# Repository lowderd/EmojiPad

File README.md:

# EmojiPad
ATmega328 Based USB HID Keyboard

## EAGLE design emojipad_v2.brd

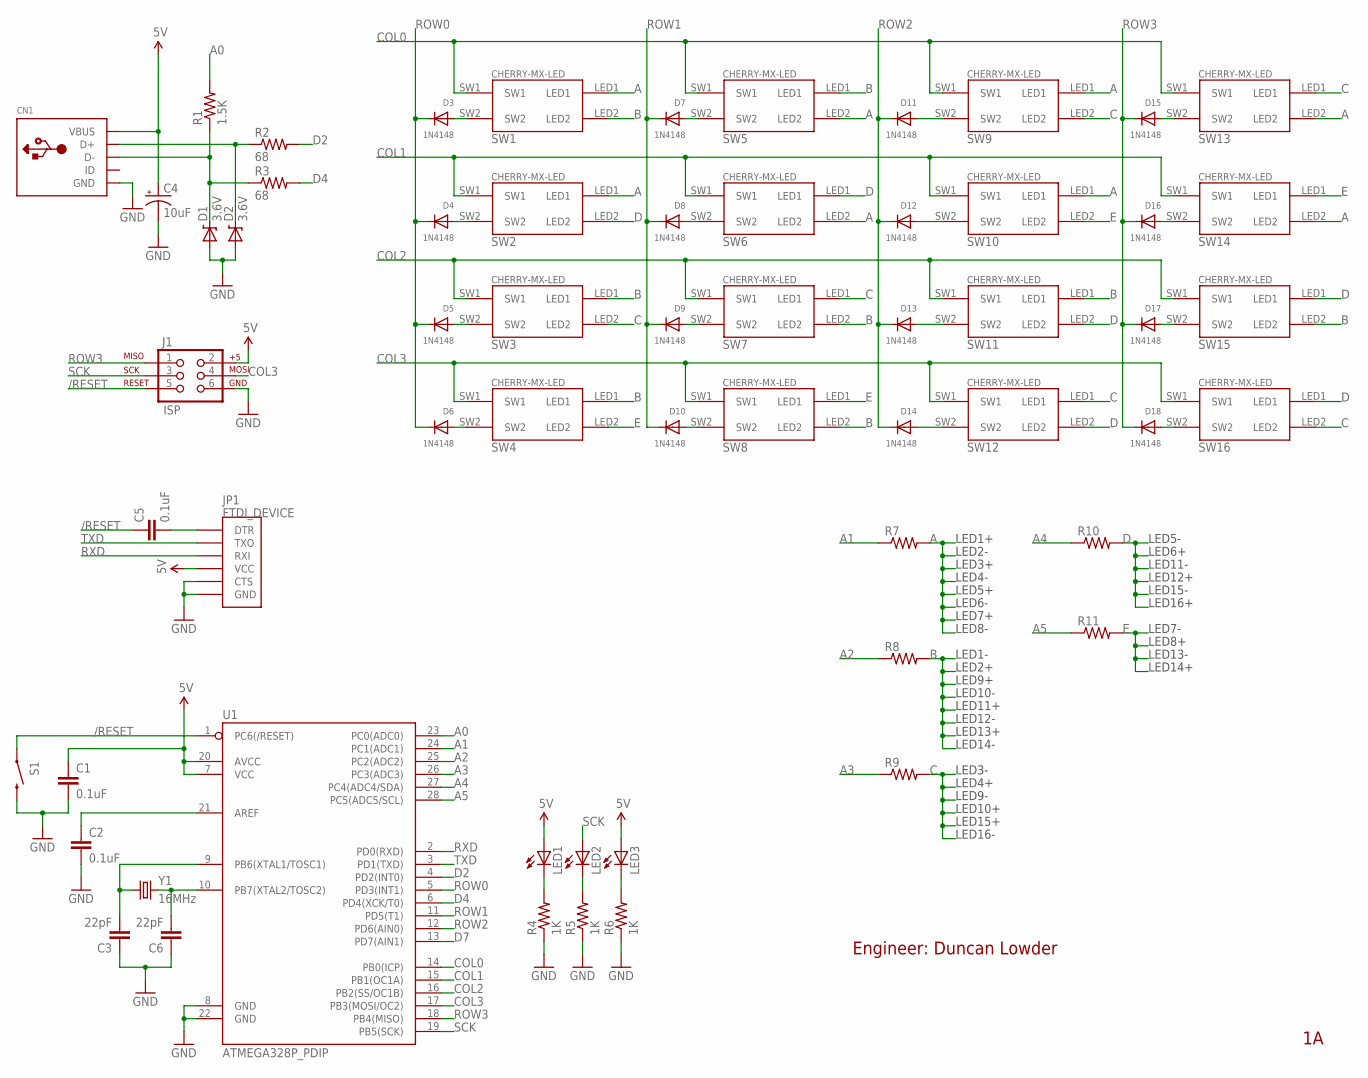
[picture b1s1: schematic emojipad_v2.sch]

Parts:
C1, C2, C5: 0.1uF; CAP-PTH-SMALL
C3, C6: 22pF; CAP-PTH-SMALL
C4: 10uF; CPOL-RADIAL-10UF-25V
CN1: USBMOLEX; USB-MINIB-THM-MOLEX
D1, D2: 3.6V; DIODE-ZENER
D3, D4, D5, D6, D7, D8, D9, D10, D11, D12, D13, D14, D15, D16, D17, D18: 1N4148; DO-1N4148
J1: ISP; 2X3
JP1: FTDI_DEVICE; FTDI_DEVICE_SIDE
LED1, LED2, LED3: LED3MM
R1: 1.5K; AXIAL-0.3
R2, R3: 68; AXIAL-0.3
R4, R5, R6: 1K; AXIAL-0.3
R7, R8, R9, R10, R11: RESISTORAXIAL-0.3; AXIAL-0.3
S1: SWITCH-MOMENTARY-2SIDE_EZ; TACTILE-PTH-SIDEEZ
SW1, SW2, SW3, SW4, SW5, SW6, SW7, SW8, SW9, SW10, SW11, SW12, SW13, SW14, SW15, SW16: CHERRY-MX-LED
U1: ATMEGA328P_PDIP; DIL28-3
Y1: 16MHz; HC49US

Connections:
5V: C1.1, C4.1 (+), CN1.VBUS, J1.2, JP1.P$4 (VCC), LED1.A, LED3.A, U1.7 (VCC), U1.20 (AVCC)
/RESET: C5.1, J1.5, S1.1, U1.1 (PC6(/RESET))
A: R7.P$2 (2), SW1.LED1, SW2.LED1, SW5.LED2, SW6.LED2, SW9.LED1, SW10.LED1, SW13.LED2, SW14.LED2
A0: R1.P$2 (2), U1.23 (PC0(ADC0))
A1: R7.P$1 (1), U1.24 (PC1(ADC1))
A2: R8.P$1 (1), U1.25 (PC2(ADC2))
A3: R9.P$1 (1), U1.26 (PC3(ADC3))
A4: R10.P$1 (1), U1.27 (PC4(ADC4/SDA))
A5: R11.P$1 (1), U1.28 (PC5(ADC5/SCL))
B: R8.P$2 (2), SW1.LED2, SW3.LED1, SW4.LED1, SW5.LED1, SW7.LED2, SW8.LED2, SW11.LED1, SW15.LED2
C: R9.P$2 (2), SW3.LED2, SW7.LED1, SW9.LED2, SW12.LED1, SW13.LED1, SW16.LED2
COL0: SW1.SW1, SW5.SW1, SW9.SW1, SW13.SW1, U1.14 (PB0(ICP))
COL1: SW2.SW1, SW6.SW1, SW10.SW1, SW14.SW1, U1.15 (PB1(OC1A))
COL2: SW3.SW1, SW7.SW1, SW11.SW1, SW15.SW1, U1.16 (PB2(SS/OC1B))
COL3: J1.4, SW4.SW1, SW8.SW1, SW12.SW1, SW16.SW1, U1.17 (PB3(MOSI/OC2))
D: R10.P$2 (2), SW2.LED2, SW6.LED1, SW11.LED2, SW12.LED2, SW15.LED1, SW16.LED1
D2: R2.P$2 (2), U1.4 (PD2(INT0))
D4: R3.P$2 (2), U1.6 (PD4(XCK/T0))
D7: U1.13 (PD7(AIN1))
D+: CN1.D+, D2.P$1 (C), R2.P$1 (1)
D-: CN1.D-, D1.P$1 (C), R1.P$1 (1), R3.P$1 (1)
E: R11.P$2 (2), SW4.LED2, SW8.LED1, SW10.LED2, SW14.LED1
GND: C1.2, C2.2, C3.1, C4.2 (-), C6.1, CN1.GND, D1.P$2 (A), D2.P$2 (A), J1.6, JP1.P$5 (CTS), JP1.P$6 (GND), R4.P$1 (1), R5.P$1 (1), R6.P$1 (1), S1.2, U1.8 (GND), U1.22 (GND)
unnamed: LED1.K (C), R4.P$2 (2)
unnamed: D3.A, SW1.SW2
unnamed: D4.A, SW2.SW2
unnamed: D5.A, SW3.SW2
unnamed: C2.1, U1.21 (AREF)
unnamed: C6.2, U1.10 (PB7(XTAL2/TOSC2)), Y1.2
unnamed: D6.A, SW4.SW2
unnamed: D7.A, SW5.SW2
unnamed: D8.A, SW6.SW2
unnamed: D9.A, SW7.SW2
unnamed: D10.A, SW8.SW2
unnamed: D11.A, SW9.SW2
unnamed: D12.A, SW10.SW2
unnamed: D13.A, SW11.SW2
unnamed: D14.A, SW12.SW2
unnamed: D15.A, SW13.SW2
unnamed: D16.A, SW14.SW2
unnamed: D17.A, SW15.SW2
unnamed: D18.A, SW16.SW2
unnamed: C3.2, U1.9 (PB6(XTAL1/TOSC1)), Y1.1
unnamed: LED2.K (C), R5.P$2 (2)
unnamed: LED3.K (C), R6.P$2 (2)
unnamed: C5.2, JP1.P$1 (DTR)
ROW0: D3.C, D4.C, D5.C, D6.C, U1.5 (PD3(INT1))
ROW1: D7.C, D8.C, D9.C, D10.C, U1.11 (PD5(T1))
ROW2: D11.C, D12.C, D13.C, D14.C, U1.12 (PD6(AIN0))
ROW3: D15.C, D16.C, D17.C, D18.C, J1.1, U1.18 (PB4(MISO))
RXD: JP1.P$3 (RXI), U1.2 (PD0(RXD))
SCK: J1.3, LED2.A, U1.19 (PB5(SCK))
TXD: JP1.P$2 (TXO), U1.3 (PD1(TXD))

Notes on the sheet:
LED1+
LED2-
LED3+
LED4-
LED5+
LED6-
LED7+
LED8-
LED1-
LED2+
LED9+
LED10-
LED11+
LED12-
LED13+
LED14-
LED3-
LED4+
LED9-
LED10+
LED15+
LED16-
LED5-
LED6+
LED11-
LED12+
LED15-
LED16+
LED7-
LED8+
LED13-
LED14+
Engineer: Duncan Lowder

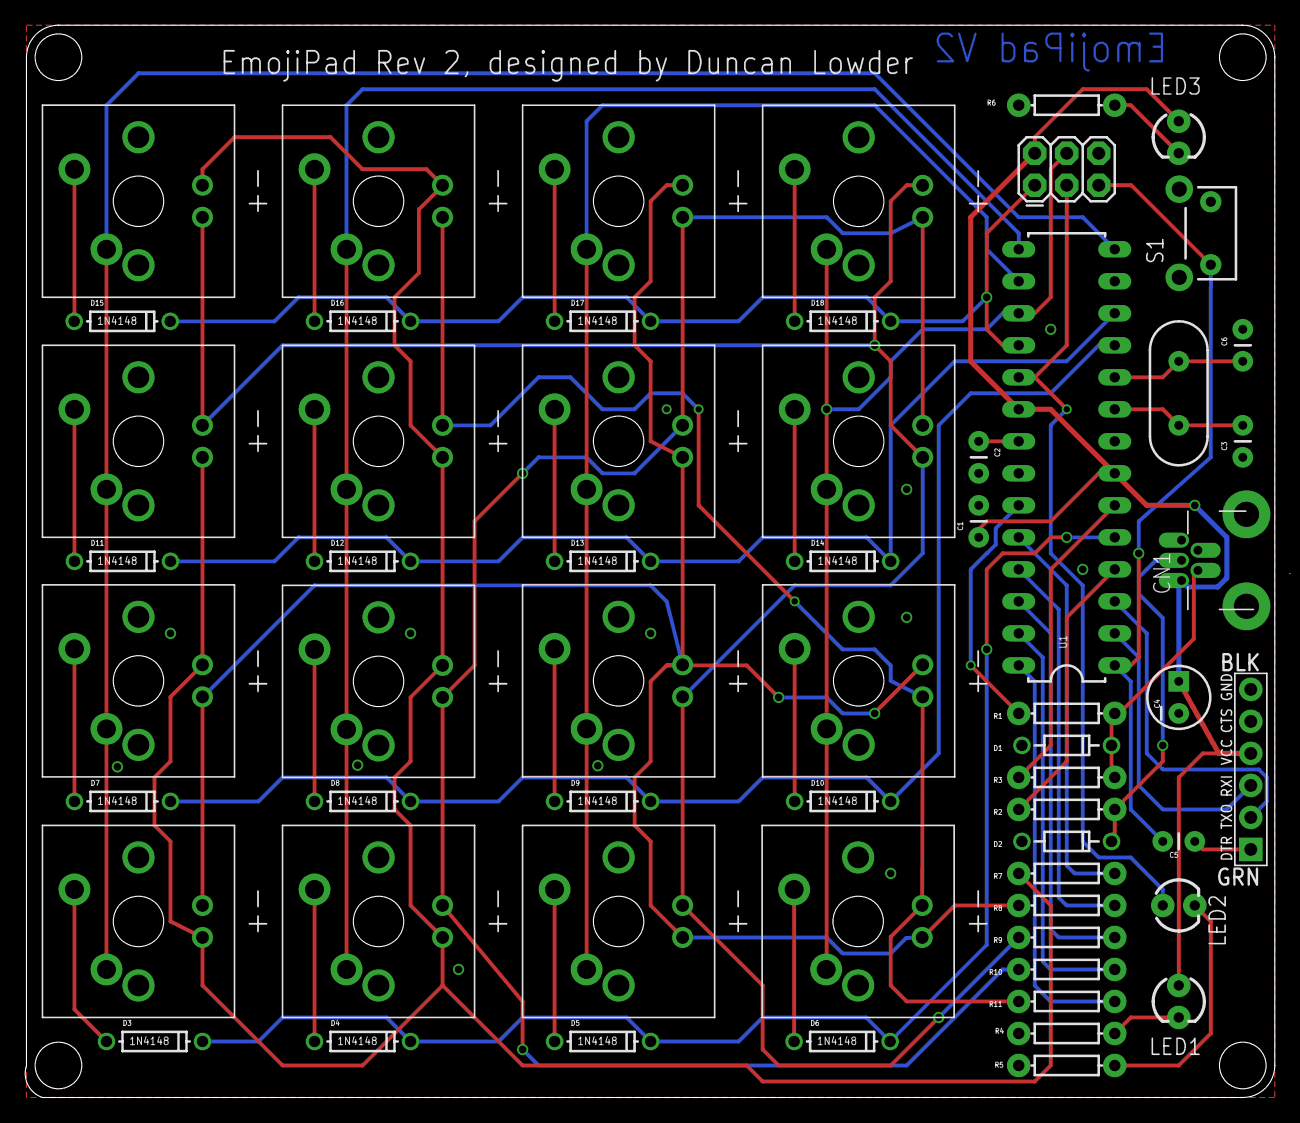
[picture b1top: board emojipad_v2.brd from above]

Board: 2 copper layers, 99.2 x 85.1 mm, 60 parts (0 on the bottom side), 52 nets.

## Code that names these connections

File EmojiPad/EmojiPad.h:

//*****************************************************************************
//* 		EmojiPad Arduino Sketch Header                                        *    
//*****************************************************************************
//
//      Creates a USB HID Device using the V-USB Library from Objective 
//      Development. This is then used to implement a 16-key keyboard, with 
//      keys mapped to different emoticons. 
//
//      Author: Duncan Lowder
//      E-Mail: duncan.lowder@gmail.com
//      Date: 2015-04-07
//      License: GNU GPL v2
//
//      Copyright (C) 2015  Duncan Lowder
//
//      This program is free software: you can redistribute it and/or modify
//      it under the terms of the GNU General Public License as published by
//      the Free Software Foundation, either version 3 of the License, or
//      (at your option) any later version.
//
//      This program is distributed in the hope that it will be useful,
//      but WITHOUT ANY WARRANTY; without even the implied warranty of
//      MERCHANTABILITY or FITNESS FOR A PARTICULAR PURPOSE.  See the
//      GNU General Public License for more details.
//
//      You should have received a copy of the GNU General Public License
//      along with this program.  If not, see <http://www.gnu.org/licenses/>.
//*****************************************************************************
#ifndef __EmojiPad_h__
#define __EmojiPad_h__

// --- Config Flags -----------------------------------------------------------
// Temporary Hardware Coniguration Flags
// These should be moved to a separate configuration file that is included 
// during compilation. 
#define EMOJI_PAD


// --- Global Constants -------------------------------------------------------

// Pin Declarations
// All pin mappings reference the default Arduino pin values, may want to 
// change this to AVR port mapping values
#ifdef EMOJI_PAD
	// Keypad Matrix Pinout
	#define COL0 3
	#define COL1 5
	#define COL2 6
	#define COL3 12
	#define ROW0 8
	#define ROW1 9
	#define ROW2 10
	#define ROW3 11

	// LED Matrix Pinout (Charliplexed)
	#define LED0 15
	#define LED1 16
	#define LED2 17
	#define LED3 18
	#define LED4 19	
#endif	// EMOJI_PAD

#ifdef FOUR_SQUARED
	// Keypad Matrix Pinout
	#define COL0 2
	#define COL1 3
	#define COL2 4
	#define COL3 5
	#define ROW0 8
	#define ROW1 9
	#define ROW2 10
	#define ROW3 11

	// LED Matrix Pinout (Standard)
	// D13 are connected to different LEDs
	#define LED_COL0 6
	#define LED_COL1 7
	#define LED_COL2 12
	#define LED_COL3 14
	#define LED_ROW0 15
	#define LED_ROW1 16
	#define LED_ROW2 18 
	#define LED_ROW3 19
#endif	// FOUR_SQUARED

#define LED  13

// Button States 
#define IDLE 		0
#define PRESSED		1
#define HOLD		2
#define RELEASED	4

// Emoticon Keyboard Key Constants
#define EB_KEY0 	1
#define EB_KEY1 	2
#define EB_KEY2 	3
#define EB_KEY3 	4
#define EB_KEY4 	5
#define EB_KEY5 	6
#define EB_KEY6 	7
#define EB_KEY7 	8
#define EB_KEY8 	9
#define EB_KEY9 	10 
#define EB_KEY10	11
#define EB_KEY11 	12 
#define EB_KEY12 	13
#define EB_KEY13 	14
#define EB_KEY14 	15
#define EB_KEY15 	16

// Pin State Definitions
#define FLOAT 	2
#define HIGH 	1
#define LOW  	0

 
// Keypad Constants
const uint8_t ROWS = 4;
const uint8_t COLS = 4;
const uint8_t MAX_KEYS_ACTIVE = 6;

// --- STRUCTURE DEFINITIONS --------------------------------------------------

// Key Structure
// This is used to keep track of the current state and hold time of an active 
// key
struct key {
	uint32_t start_time;	// Timestamp of when the key was initially pressed
	uint8_t key_value;		// Value associated with the pressed key
	uint8_t key_state;		// Current state of the key
};


// --- GLOBAL VARIABLE DEFINITIONS --------------------------------------------

// Column and Row Pin Definitions
uint8_t colPins[COLS] = {COL0, COL1, COL2, COL3};
uint8_t rowPins[ROWS] = {ROW0, ROW1, ROW2, ROW3};

// Key Value Map
// This contains the map of the keypad matrix and it's associated values. This
// list is used to assign the value of a currently active key. 
uint8_t keys[ROWS][COLS] = {
	{ EB_KEY0,  EB_KEY1,  EB_KEY2,  EB_KEY3},
	{ EB_KEY4,  EB_KEY5,  EB_KEY6,  EB_KEY7},
	{ EB_KEY8,  EB_KEY9, EB_KEY10, EB_KEY11},
	{EB_KEY12, EB_KEY13, EB_KEY14, EB_KEY15}
};

// Bitmap for determining active keys
uint8_t bit_map[ROWS];

// List containing the active keys state information
key keys_active[MAX_KEYS_ACTIVE];

uint32_t start_time;
uint32_t debounce_time = 10;
uint32_t hold_time = 250;

uint32_t prevTime;
uint32_t elapsedTimeMs;
int lastState = LOW; // LOW is equivalent to 0

#endif // __EmojiPad_h__

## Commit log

2015-04-09 Initial Commit of EmojiPad Hardware and Firmware Files
2015-04-11 Update to EmojiPad Sketch Files, Modification to V2 of the PCB: Changed pull-up to a GPIO pin, and D- to D12, Initial 3D Model Check In
2015-04-12 Finished Model of Rev 2 of the PCBA
2015-04-13 Added EmojiPad Case files, P2 Size for Ponoko Laser Cutting
2015-04-13 Removed Google Sketchup Keymapping
2015-04-13 Modification to Emoji Key Map
2015-04-18 Add GPLv2 License to project
2015-05-21 Added mapping for new board using membrane keyswitches"
2015-07-15 EmojiPad PCB Rev2 Ready for Order
2015-07-15 V2 BOM

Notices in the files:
parts and their libraries:
SparkFun-Connectors: Licensing: Creative Commons ShareAlike 4.0 International - https://creativecommons.org/licenses/by-sa/4.0
